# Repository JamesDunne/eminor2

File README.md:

Read more about this project at http://eminor2.bittwiddlers.org/

The repository is split into two versions of the project, v1 and v2.

v1 is the original eminor project created in 2007 and exists as a single prototype unit. Read more about that project here: http://bittwiddlers.org/e-minor/. I continued hacking on this project well into the design and production of v2 so that I could still have a functional MIDI controller. Its code and project files are kept around for posterity now.

v2 corresponds to the more recent eminor2 project, started in 2013. I designed v2 based on the shortcomings of v1, notably the lack of enough footswitches and the physical spacing between the footswitches. The v2 has twice as many footswitches as the v1, and has one LED per each footswitch for simple signalling UX purposes. The v2 also sports a 40x4 character LCD screen which is a notable improvement over the 5x 7-segment LED display on the v1.

Each project folder is split into `controller` and `PCB`. `controller` contains all the C and microcontroller assembly source code for the firmware controller logic. `PCB` contains all the schematics, drawings, and design files for the hardware portion.

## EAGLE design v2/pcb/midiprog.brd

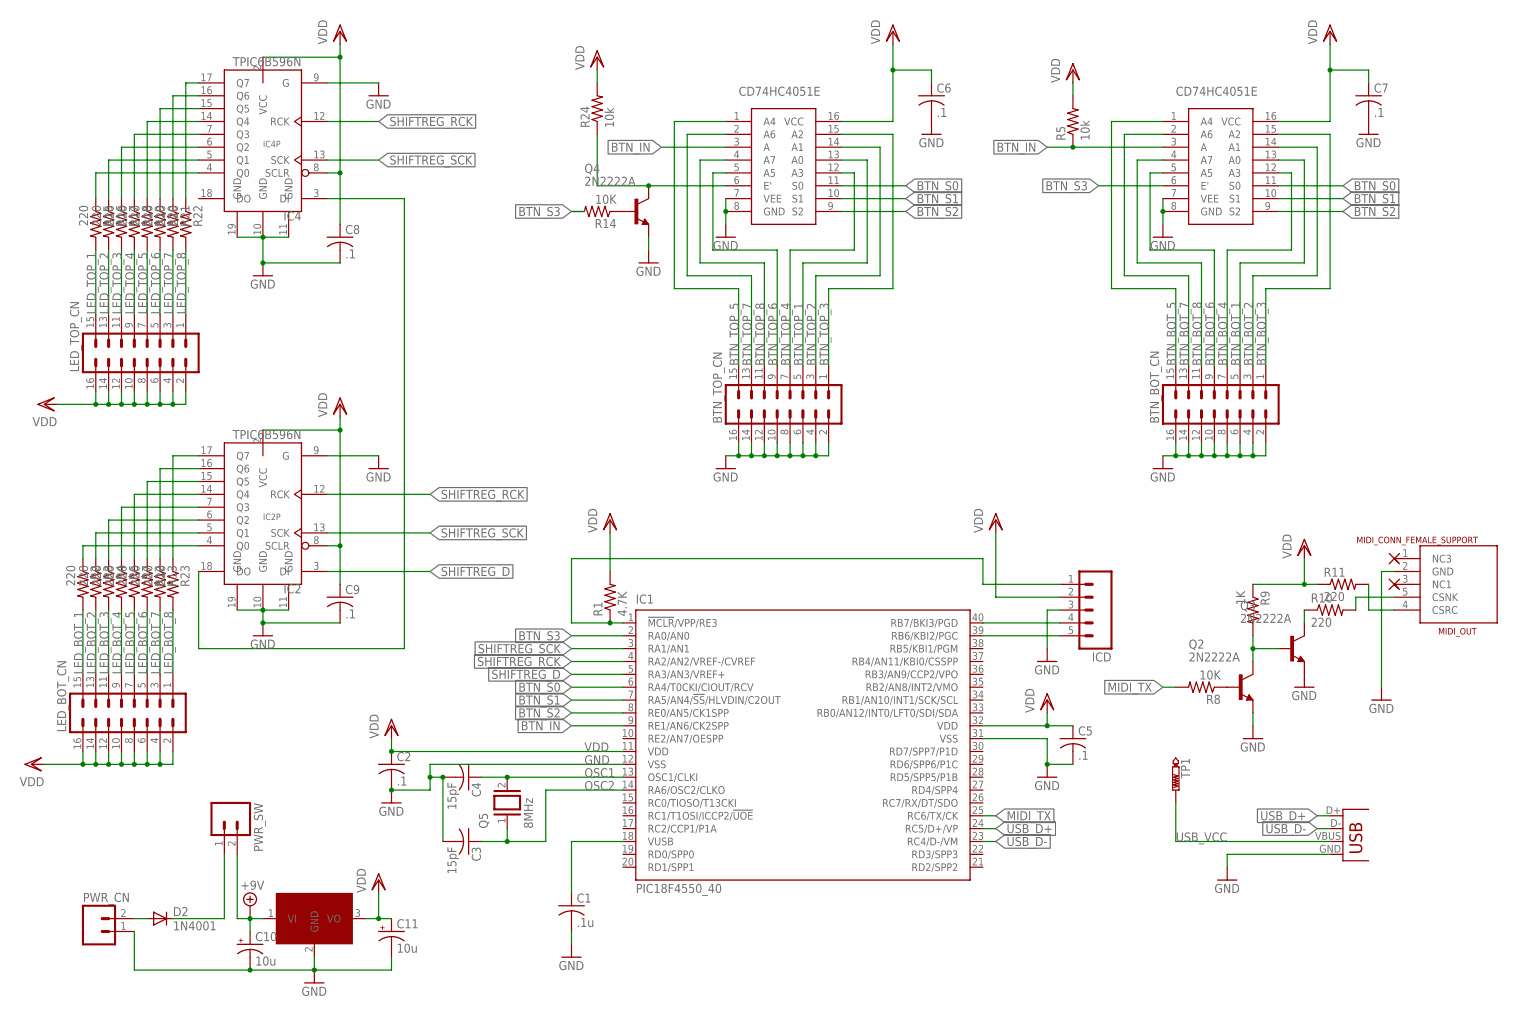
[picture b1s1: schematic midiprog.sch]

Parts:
BTN_BOT_CN: MA08-2
BTN_TOP_CN: MA08-2
C1: .1u; C050-025X075
C2, C5, C6, C7, C8, C9: .1; C050-025X075
C3, C4: 15pF; C050-025X075
C10, C11: 10u; E2,5-6
D2: 1N4001; DO41-10
IC1: PIC18F4550_40; DIL40
IC2, IC4: TPIC6B596N; DIL20
ICD: MA05; 05PA
JP1: USB-B; USB-B-PTH
LED_BOT_CN: MA08-2
LED_TOP_CN: MA08-2
MIDI_OUT: MIDI_CONN_FEMALE_SUPPORT; DIN_5_FEMALE_SUPPORT
PWR_CN: M02; 02P
PWR_SW: M02; 02P
Q2, Q3, Q4: 2N2222A; TO18
Q5: 8MHz; QS
R1: 4.7K; 0207/10
R2, R3, R4, R6, R7, R10, R11, R12, R13, R15, R16, R17, R18, R19, R20, R21, R22, R23: 220; 0207/10
R5, R24: 10k; 0207/10
R8, R14: 10K; 0207/10
R9: 1K; 0207/10
TP1: PTR1PAD1-17; P1-17
U$1, U$2: CD74HC4051E
U$3: 7805; JKDFJD

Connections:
+9V: C10.+, PWR_SW.2, U$3.1 (VI)
BTN_BOT_1: BTN_BOT_CN.5, U$1.13 (A0)
BTN_BOT_2: BTN_BOT_CN.3, U$1.14 (A1)
BTN_BOT_3: BTN_BOT_CN.1, U$1.15 (A2)
BTN_BOT_4: BTN_BOT_CN.7, U$1.12 (A3)
BTN_BOT_5: BTN_BOT_CN.15, U$1.1 (A4)
BTN_BOT_6: BTN_BOT_CN.9, U$1.5 (A5)
BTN_BOT_7: BTN_BOT_CN.13, U$1.2 (A6)
BTN_BOT_8: BTN_BOT_CN.11, U$1.4 (A7)
BTN_IN: IC1.9 (RE1/AN6/CK2SPP), R5.1, U$1.3 (A), U$2.3 (A)
BTN_S0: IC1.6 (RA4/T0CKI/CIOUT/RCV), U$1.11 (S0), U$2.11 (S0)
BTN_S1: IC1.7 (RA5/AN4/!SS!/HLVDIN/C2OUT), U$1.10 (S1), U$2.10 (S1)
BTN_S2: IC1.8 (RE0/AN5/CK1SPP), U$1.9 (S2), U$2.9 (S2)
BTN_S3: IC1.2 (RA0/AN0), R14.2, U$1.6 (E')
BTN_TOP_1: BTN_TOP_CN.5, U$2.13 (A0)
BTN_TOP_2: BTN_TOP_CN.3, U$2.14 (A1)
BTN_TOP_3: BTN_TOP_CN.1, U$2.15 (A2)
BTN_TOP_4: BTN_TOP_CN.7, U$2.12 (A3)
BTN_TOP_5: BTN_TOP_CN.15, U$2.1 (A4)
BTN_TOP_6: BTN_TOP_CN.9, U$2.5 (A5)
BTN_TOP_7: BTN_TOP_CN.13, U$2.2 (A6)
BTN_TOP_8: BTN_TOP_CN.11, U$2.4 (A7)
GND: BTN_BOT_CN.2, BTN_BOT_CN.4, BTN_BOT_CN.6, BTN_BOT_CN.8, BTN_BOT_CN.10, BTN_BOT_CN.12, BTN_BOT_CN.14, BTN_BOT_CN.16, BTN_TOP_CN.2, BTN_TOP_CN.4, BTN_TOP_CN.6, BTN_TOP_CN.8, BTN_TOP_CN.10, BTN_TOP_CN.12, BTN_TOP_CN.14, BTN_TOP_CN.16, C1.2, C2.2, C3.2, C4.2, C5.2, C6.2, C7.2, C8.2, C9.2, C10.-, C11.-, IC1.12 (VSS), IC1.31 (VSS), IC2.9 (G), IC2.10 (GND), IC2.11 (GND), IC2.19 (GND), IC4.9 (G), IC4.10 (GND), IC4.11 (GND), IC4.19 (GND), ICD.3, JP1.GND, MIDI_OUT.2 (GND), PWR_CN.1, Q2.1 (E), Q3.1 (E), Q4.1 (E), U$1.7 (VEE), U$1.8 (GND), U$2.7 (VEE), U$2.8 (GND), U$3.2 (GND)
LED_BOT_1: LED_BOT_CN.15, R2.2
LED_BOT_2: LED_BOT_CN.13, R3.2
LED_BOT_3: LED_BOT_CN.11, R4.2
LED_BOT_4: LED_BOT_CN.9, R6.2
LED_BOT_5: LED_BOT_CN.7, R7.2
LED_BOT_6: LED_BOT_CN.5, R12.2
LED_BOT_7: LED_BOT_CN.3, R13.2
LED_BOT_8: LED_BOT_CN.1, R23.2
LED_TOP_1: LED_TOP_CN.15, R15.2
LED_TOP_2: LED_TOP_CN.13, R16.2
LED_TOP_3: LED_TOP_CN.11, R17.2
LED_TOP_4: LED_TOP_CN.9, R18.2
LED_TOP_5: LED_TOP_CN.7, R19.2
LED_TOP_6: LED_TOP_CN.5, R20.2
LED_TOP_7: LED_TOP_CN.3, R21.2
LED_TOP_8: LED_TOP_CN.1, R22.2
MIDI_TX: IC1.25 (RC6/TX/CK), R8.2
unnamed: IC1.1 (!MCLR!/VPP/RE3), ICD.1, R1.1
unnamed: Q2.2 (B), R8.1
unnamed: Q2.3 (C), Q3.2 (B), R9.2
unnamed: Q3.3 (C), R10.1
unnamed: MIDI_OUT.4 (CSRC), R11.2
unnamed: MIDI_OUT.5 (CSNK), R10.2
unnamed: IC1.39 (RB6/KBI2/PGC), ICD.5
unnamed: IC1.40 (RB7/BKI3/PGD), ICD.4
unnamed: C1.1, IC1.18 (VUSB)
unnamed: IC4.4 (Q0), R15.1
unnamed: IC4.5 (Q1), R16.1
unnamed: IC4.6 (Q2), R17.1
unnamed: IC4.7 (Q3), R18.1
unnamed: IC4.14 (Q4), R19.1
unnamed: IC4.15 (Q5), R20.1
unnamed: IC4.16 (Q6), R21.1
unnamed: IC4.17 (Q7), R22.1
unnamed: IC2.18 (DO), IC4.3 (DI)
unnamed: D2.A, PWR_CN.2
unnamed: D2.C, PWR_SW.1
unnamed: IC2.4 (Q0), R2.1
unnamed: IC2.5 (Q1), R3.1
unnamed: IC2.6 (Q2), R4.1
unnamed: IC2.7 (Q3), R6.1
unnamed: IC2.14 (Q4), R7.1
unnamed: IC2.15 (Q5), R12.1
unnamed: IC2.16 (Q6), R13.1
unnamed: IC2.17 (Q7), R23.1
unnamed: Q4.2 (B), R14.1
unnamed: Q4.3 (C), R24.1, U$2.6 (E')
OSC1: C4.1, IC1.13 (OSC1/CLKI), Q5.2
OSC2: C3.1, IC1.14 (RA6/OSC2/CLKO), Q5.1
SHIFTREG_D: IC1.5 (RA3/AN3/VREF+), IC2.3 (DI)
SHIFTREG_RCK: IC1.4 (RA2/AN2/VREF-/CVREF), IC2.12 (RCK), IC4.12 (RCK)
SHIFTREG_SCK: IC1.3 (RA1/AN1), IC2.13 (SCK), IC4.13 (SCK)
USB_D+: IC1.24 (RC5/D+/VP), JP1.D+
USB_D-: IC1.23 (RC4/D-/VM), JP1.D-
USB_VCC: JP1.VBUS, TP1.TP
VDD: C2.1, C5.1, C6.1, C7.1, C8.1, C9.1, C11.+, IC1.11 (VDD), IC1.32 (VDD), IC2.2 (VCC), IC2.8 (SCLR), IC4.2 (VCC), IC4.8 (SCLR), ICD.2, LED_BOT_CN.2, LED_BOT_CN.4, LED_BOT_CN.6, LED_BOT_CN.8, LED_BOT_CN.10, LED_BOT_CN.12, LED_BOT_CN.14, LED_BOT_CN.16, LED_TOP_CN.2, LED_TOP_CN.4, LED_TOP_CN.6, LED_TOP_CN.8, LED_TOP_CN.10, LED_TOP_CN.12, LED_TOP_CN.14, LED_TOP_CN.16, R1.2, R5.2, R9.1, R11.1, R24.2, U$1.16 (VCC), U$2.16 (VCC), U$3.3 (VO)

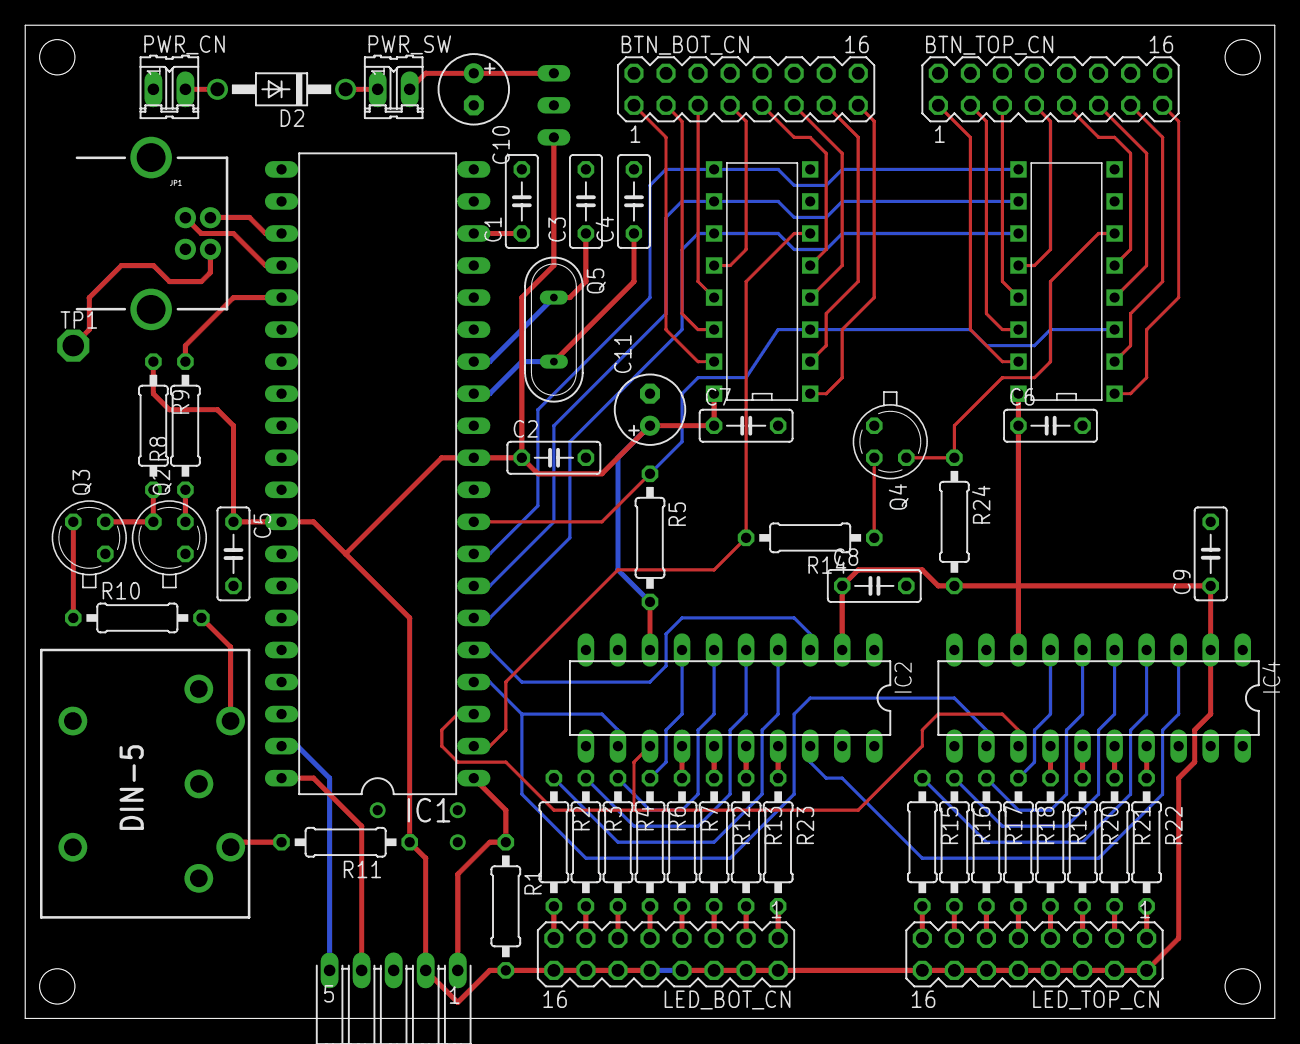
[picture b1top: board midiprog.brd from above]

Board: 2 copper layers, 99.1 x 78.7 mm, 56 parts (0 on the bottom side), 79 nets.

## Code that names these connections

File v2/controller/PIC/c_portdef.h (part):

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
//PORTA Definitions
#define BTN_S3_BIT                      0
#define BTN_S3_PIN                      PORTAbits.RA0   //Pin 2
#define BTN_S3_LAT_BIT                  LATAbits.LATA0
#define BTN_S3_LAT                      LATA
#define BTN_S3_TRIS_BIT                 TRISAbits.TRISA0
#define BTN_S3_PORT                     PORTA
#define TRISAPIN0                       (OUTPUT<<0)
#define LATAPIN0                        (false<<0)

#define SHIFTREG_SRCK_BIT               1
#define SHIFTREG_SRCK_PIN               PORTAbits.RA1   //Pin 3
#define SHIFTREG_SRCK_LAT_BIT           LATAbits.LATA1
#define SHIFTREG_SRCK_LAT               LATA
#define SHIFTREG_SRCK_TRIS_BIT          TRISAbits.TRISA1
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#define LATAPIN1                        (false<<1)

#define SHIFTREG_RCK_BIT                2
#define SHIFTREG_RCK_PIN                PORTAbits.RA2   //Pin 4
#define SHIFTREG_RCK_LAT_BIT            LATAbits.LATA2
#define SHIFTREG_RCK_LAT                LATA
#define SHIFTREG_RCK_TRIS_BIT           TRISAbits.TRISA2
#define SHIFTREG_RCK_PORT               PORTA
#define TRISAPIN2                       (OUTPUT<<2)
#define LATAPIN2                        (false<<2)

#define SHIFTREG_SER_IN_BIT             3
#define SHIFTREG_SER_IN_PIN             PORTAbits.RA3   //Pin 5
#define SHIFTREG_SER_IN_LAT_BIT         LATAbits.LATA3
#define SHIFTREG_SER_IN_LAT             LATA
#define SHIFTREG_SER_IN_TRIS_BIT        TRISAbits.TRISA3
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#define LATAPIN3                        (false<<3)

#define BTN_S0_BIT                      4
#define BTN_S0_PIN                      PORTAbits.RA4   //Pin 6
#define BTN_S0_LAT_BIT                  LATAbits.LATA4
#define BTN_S0_LAT                      LATA
#define BTN_S0_TRIS_BIT                 TRISAbits.TRISA4
#define BTN_S0_PORT                     PORTA
#define TRISAPIN4                       (OUTPUT<<4)
#define LATAPIN4                        (false<<4)

#define BTN_S1_BIT                      5
#define BTN_S1_PIN                      PORTAbits.RA5   //Pin 7
#define BTN_S1_LAT_BIT                  LATAbits.LATA5
#define BTN_S1_LAT                      LATA
#define BTN_S1_TRIS_BIT                 TRISAbits.TRISA5
#define BTN_S1_PORT                     PORTA
#define TRISAPIN5                       (OUTPUT<<5)
#define LATAPIN5                        (false<<5)

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#define LATBPIN5                        (false<<5)

#define UNUSED1_OFF_BIT                 6
#define UNUSED1_PIN                     PORTBbits.RB6   //Pin 39
#define UNUSED1_LAT_BIT                 LATBbits.LATB6
#define UNUSED1_LAT                     LATB
#define UNUSED1_TRIS_BIT                TRISBbits.TRISB6
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#define LATBPIN6                        (false<<6)

#define UNUSED2_BIT                     7
#define UNUSED2_PIN                     PORTBbits.RB7   //Pin 40
#define UNUSED2_LAT_BIT                 LATBbits.LATB7
#define UNUSED2_LAT                     LATB
#define UNUSED2_TRIS_BIT                TRISBbits.TRISB7
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#define LATCPIN3                        (false<<3)

#define USBDM_BIT                       4
#define USBDM_PIN                       PORTCbits.RC4   //Pin 23
#define USBDM_LAT_BIT                   LATCbits.LATC4
#define USBDM_LAT                       LATC
#define USBDM_TRIS_BIT                  TRISCbits.TRISC4
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#define LATCPIN4                        (false<<4)

#define USBDP_BIT                       5
#define USBDP_PIN                       PORTCbits.RC5   //Pin 24
#define USBDP_LAT_BIT                   LATCbits.LATC5
#define USBDP_LAT                       LATC
#define USBDP_TRIS_BIT                  TRISCbits.TRISC5
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#define LATCPIN5                        (false<<5)

#define TX_BIT                          6
#define TX_PIN                          PORTCbits.RC6   //Pin 25
#define TX_LAT_BIT                      LATCbits.LATC6
#define TX_LAT                          LATC
#define TX_TRIS_BIT                     TRISCbits.TRISC6
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//++++++++++++++++++++++++++++++++++++++++++++++++++++++++++++++++++++++++++++++
//PORTE Definitions
#define BTN_S2_BIT                      0
#define BTN_S2_PIN                      PORTEbits.RE0   //Pin 8
#define BTN_S2_LAT_BIT                  LATEbits.LATE0
#define BTN_S2_LAT                      LATE
#define BTN_S2_TRIS_BIT                 TRISEbits.TRISE0
#define BTN_S2_PORT                     PORTE
#define TRISEPIN0                       (OUTPUT<<0)
#define LATEPIN0                        (false<<0)

#define BTN_IN_BIT                      1
#define BTN_IN_PIN                      PORTEbits.RE1   //Pin 9
#define BTN_IN_LAT_BIT                  LATEbits.LATE1
#define BTN_IN_LAT                      LATE
#define BTN_IN_TRIS_BIT                 TRISEbits.TRISE1
#define BTN_IN_PORT                     PORTE
#define TRISEPIN1                       (INPUT<<1)
#define LATEPIN1                        (false<<1)

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
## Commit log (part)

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2017-07-05 Allow unnamed songs to be editable.
2017-07-05 Recompiled html5.
2017-07-05 Rebuilt HEX.
2017-08-01 Updated setlist for next show. Rebuilt HEX.
2017-08-01 Updated venue
2017-08-05 Rebuilt on new install as test. Updated project with relative paths instead of hard-coded C:\ paths.
2017-08-13 Updated axe-fx
2017-08-13 Updated axe-fx to match black album tone
2017-08-13 Updated tone slightly
2017-08-13 Fix win32 midi device number in debug settings
2017-08-15 Ideal Sandman tone
2017-08-15 Improved input trim curve to not cause clean sound to clip too much
2017-08-16 Switched Win32 driver to parse MIDI out device by name from command line.
2017-08-16 Save before tweak
2017-08-16 Closer to sandman... need more low end, less mid.
2017-08-16 Fixed Trippin
2017-08-16 Log-taper the gain from the yaml file; TODO make this permanent.
2017-08-16 Fix volume curves, gates, and compressor settings.
2017-08-16 Rebuilt HEX
2017-08-17 Even closer
2017-08-17 Less harshness in upper mids.
2017-08-17 Perfect
2017-08-21 Fixed html5 bug in formatting signed 8-bit values as hex.
2017-08-21 Require allow/block MIDI access before starting controller.
2017-08-21 Fix midi log width
2017-08-21 Working midi send.
2017-08-22 Upgraded volume curves on amps.
2017-08-22 Drop-down to select MIDI device.
2017-09-06 flash_manager now generates songs.tsv
2017-09-06 Updated headers.
2017-09-07 New setlist
2017-09-22 Fix toolset
2017-09-22 Remove old flash_manager.
2017-09-22 Set up Win32 project.
2017-09-22 Set up PIC build
2017-09-22 Reorganize functions.
2017-09-22 Tweaked LCD design; added design of custom FX selector.
2017-09-22 Redesigned AMP controls slightly for quicker access to more commonly used features (reset volume or gain to default)
2017-09-22 Document Axe-FX changes a bit better; TODOs for desired features.
2017-09-22 Clarified gain store/recall behavior. Consistency on other screens.
2017-09-22 Clarify FX selection behavior and LCD response.
2017-09-23 Update axe-fx programs and create new v5.
2017-09-23 Update v5 axe-fx
2017-09-23 Dont assume PITCH effect due to high CPU usage of basic 2-amp template.
2017-09-23 Starting to make row modes.
2017-09-25 Rewrote portion of button control; FX enable/disable and clean/dirty/acoustic switch
2017-09-25 Remove XY code
2017-09-25 chmod +x
2017-09-25 Fix compiler errors
2017-09-25 Implemented main AMP controls.
2017-09-25 Update html5 build for v5
2017-09-25 Fixed bugs.
2017-09-25 Fix dumb bugs on LCD.
2017-09-25 Correct release semantics depending on oneshot or repeater. Disable acoustic when tap on clean/dirty.
2017-09-25 Highlight LED of button indicating < or > gain or volume.
2017-09-26 Recompiled html5
2017-09-26 Fixed XY behavior for clean/dirty vs. acoustic. Fixed bad CC number.
2017-09-26 Fix LCD display
2017-09-26 Fix LCD display with fx
2017-09-26 Keep FX LED on in FX mode.
2017-09-26 make debug reload to reload current chrome tab
2017-09-30 Moved program-specific structs out to separate .h file to be reused by flash_manager.
2017-09-30 Updates for vs_code
2017-09-30 Fixed separation concerns.
2017-09-30 Added custom fx_layouts
2017-09-30 Move BankedWriter out to separate file.
2017-09-30 Fix FX names to be for amp1 or 2.
2017-09-30 Rebuilt PIC flash banks.
2017-09-30 Fix NUL char to write as 0.
2017-10-01 Recompile html5
2017-10-01 Redefine set_list structure to allow 127 songs and remove date since it is not displayed any longer.
2017-10-01 Corrected flash addresses to load/store; relaxed flash_load constraints regarding 64-byte boundary.
2017-10-01 Fix bug counting setlist size.
2017-10-01 Split gain to gain_log; evaluate default logic.
2017-10-01 Fix off by one bug in song count display; update LCD when toggle mode.
2017-10-01 Add scene_count field.
2017-10-01 Show scene count on LCD
2017-10-01 Fix macro bug
2017-10-02 Fix hardware flash size for html5.
2017-10-03 Send FX MIDI changes; document amp changing MIDI.
2017-10-21 Removed selected_amp state.
2017-10-21 Set/restore default gain is a bad idea.
2017-10-21 Fix toggle acoustic off to not flip clean/dirty as well.
2017-10-21 Moved rowstate into state
2017-10-21 Start of changing button labels when switching to FX mode.
2017-10-21 Shortened fx names to 4 chars for display on LCD and HWLABELS.
2017-10-21 Fix debug log of fx name.
2017-10-21 Fixups for PIC build.
2017-10-24 Remove SAVE function, replace with TAP|MODE. Remove incomplete SELECTFX mode. Upper/lowercase FX names based on enabled/disabled.
2017-10-24 Update PIC
2017-10-24 Cleaning up #pragmas for PIC and cutting down ROM+RAM requirements.
2017-10-24 Fix PIC ROM pages so that flash is set at correct offset for 12KB length.
2017-10-24 Condensed code by not requiring mode_leds array.
2017-10-24 Upper/lowercase letters on AMP row for FX.
2017-10-25 Fixed flash manager to use same names.
2017-10-25 Rebuilt PIC
2017-10-25 Tiny code size improvements.
2017-10-25 More tiny improvements.
2017-10-25 Tightening up code memory.
2017-11-09 Removed redundant Kids entry.
2017-11-09 Create new set list
2017-11-17 Fixed gate bug when switching between acoustic and electric.
2017-11-17 Recompile html
2017-11-18 Reduce acoustic gain to avoid clipping.
2017-11-18 Keeping Axe-FX patches.
2017-11-18 Fix clean/acoustic switching so clean uses amp Y.
2017-11-18 Add new Axe-FX presets.
2017-11-25 Disable amp for acoustic. Start using global variable for clean_gain adjustment.
2017-11-25 Use original midi program numbers now.
2017-11-25 Updated Axe-FX MIDI OUT name; it changed for some reason.
2017-12-01 Added Sandman tone.
2017-12-01 Added new set list.
2017-12-01 Update setlist order.
2017-12-01 Update setlists
2017-12-02 Updated setlist to remove acoustic set.
2018-02-05 Remove binary
2018-02-05 Added new songs Creep and Go My Way
2018-02-28 Rebuilt HEX for v1
2018-03-01 ASCII art
2018-03-08 Rebuild html5
2018-03-14 Starting work on flexible amp channels regarding what CCs to enable/disable for amp channel switching.
2018-03-14 Build html5
2018-03-28 Added new set list
2018-03-28 Remove a few unused songs.
2018-04-12 Dump of new v8 tones - highlight is puppets using new Silent Underground Puppets FW Q9.04.
2018-05-18 Updated puppets v8
2018-08-08 Updated programs, new setlist.
2018-08-08 Updated HEX build
2018-08-13 Replace TAP with previous scene.
2018-08-13 Fix bad code
2018-08-15 Update clean gain from 0x10 to 0x12.
2018-08-22 Only allow next/prev scene after a retrigger timeout.
2018-09-26 Minor program tweaks for better balance.
2018-09-26 New setlist.
2018-12-12 Added new setlist; added new programs for Under the Bridge and Slide.
2018-12-12 Updated HEX
2019-02-06 Added new setlist for 2/23
2019-02-17 Replaced phasers with flangers for better Crawling tone.
2019-02-17 Updated html5 Makefile to include PIC headers.
2019-02-23 Moved Lump in setlist
2019-02-23 Build HEX
2019-04-24 Updated html5 build
2019-04-30 Rebuild html5.
2019-05-03 Updated Fuel gain and volumes
2019-05-04 Updated Puppets settings
2019-05-15 New set list
2019-05-15 Update html5 build
2019-05-15 Updated label for SCENE-- button
2019-06-04 Created setlist-generator and updated song-names.yml to mark deprecated songs.
2019-06-04 Clip shuffled song list to commandline argument as integer
2019-06-16 Updated song list for private party
2019-06-20 Added new setlist
2019-06-29 Add default gate setting at song level.
2019-06-29 Reduce default gate to -42dB
2019-07-01 Compilable v6
2019-07-01 Restructured amp_defaults to be shared between both amps.
2019-07-01 Write new flash_manager_v6 to emit v6 compatible headers.
2019-07-01 Fix padding issues
2019-07-01 Assert offsets of romdata fields
2019-07-01 Generate PIC headers
2019-07-01 Update html5 build to actually use v6 headers
2019-07-01 Fix bug with not setting sent CC values in cache.
2019-07-01 Zero out gate valuess
2019-07-01 Convert gate threshold from dB to MIDI
2019-07-01 Fix html5 sysex bug where messages were not clearing between F7 to F0
2019-07-01 Reintroduce BYP of GATE block instead of setting threshold down to a minimal value
2019-07-01 Make song-default gain and gate actually apply
2019-07-01 Fix PIC build but has buggy LCD display
2019-07-02 Small update
2019-07-02 Fix inc/dec from 0 bug
2019-07-02 Saving code space by converting macros to functions
2019-07-02 Translate gain_log to gain in v6
2019-07-02 Rebuild PIC
2019-07-02 Add td50_midi mappings to change drum kits per song
2019-07-02 Rebuilt HEX with slight code savings
2019-07-02 Designing and documenting new interface layout
2019-07-03 Remove unused bits
2019-07-03 Revert "Simplify calc_midi"
    This reverts commit c143f57dda9c36dfec1121d6a864a09828f087e9.
2019-07-03 Simple code reuse for LCD AMP rows
2019-07-03 Switch LCD amp rows to new design
2019-07-03 Implemented button and LED logic for new control layouts
2019-07-03 Fix AMP|FX toggle in MIDI screen
2019-07-03 Fix MIDI inc/dec logic to respect bounds
2019-07-03 Swapped GATE and VOLU button pairs. Removing extra timers not needed.
2019-07-03 Tiny effort to conserve code space on PIC
2019-07-03 Update HEX
2019-07-03 Fix html5 build to include left/right arrow chars from LCD charset.
2019-07-06 Updated Win32 build
2019-07-06 Enable extended-mode for PIC18 build.
2019-07-06 Revert "Enable extended-mode for PIC18 build."
    This reverts commit 284a6e4c9860e963f2dde31ccaf276411839a0cd.
2019-07-06 Remove calculation of modified status; added load_axe_midi() function and calls to it to reload axe_midi pointer when modifying axe_midi_program.
2019-07-06 Updated PIC build
2019-07-06 Consistent near pointers; did not have any effect on code size though
2019-07-06 Use anonymous struct within union to make u16 copies of io16 easier.
2019-07-06 Rebuilt HEX; saved code space with u16 in union
2019-07-06 Resize midi log display in html5
2019-07-06 Add TODO items
2019-07-06 Update controller logic to expect only 4 FX instead of 5.
2019-07-06 Add buttons in FX screen to toggle using default gain, gate, and volume.
2019-07-06 Removed unused functions
2019-07-06 Update TODO items and screens
2019-07-06 Allow selecting new song without activating scene 1 until scene++ button is pressed.
2019-07-06 Remove song_name pointer in favor next_pr_num
2019-07-06 Fix song_name declaration
2019-07-08 Upgrade html5 to use B key from USB footswitch to bind to SCENE++ button.
2019-07-09 Extended mode is bad and failed to start, might be due to bootloader embedded code.
2019-07-09 Implemented midi_send_sysex_buffer for PIC
2019-07-10 Remove old flash managers
2019-07-10 Fixed bug with setting lowest gate value at 0 instead of 1
2019-07-10 Limit song number to max_song_count
2019-07-10 Initialize defaults for uninitialized songs
2019-07-12 Corrected alternative ritoa implementation with simple unit test program.
2019-07-14 Implement simple time marker delta and interval tracking system to make TAP TEMPO LED blink in tempo.
2019-07-15 Add timer support to PIC hwcalls.c and systick.c; UNTESTED
2019-07-29 Corrected timer to use 1ms ticks instead of 10ms ticks.
2019-07-30 Add LOOPER screen with buttons and LEDs.
2019-07-30 Made PIC backend sensitive to WRITABLE_SEG_LEN in all but linker file. Updated flash_manager_v6 to also use flash.h definitions.
2019-07-30 Added LCD data sheet
2019-07-30 Tighten up timing for handling buttons, LEDs, and controller code
2019-07-30 Debounce buttons properly to 125msec and responding to button-down events within 1msec.
2019-07-31 Update html5
2019-07-31 New setlist and updated programs for gate and leveling
2019-07-31 Update repeater timers; need to add debounce release feature.
2019-08-02 Rename bypass to enable for looper since that makes more sense the way its used.
2019-08-02 Set looper ONCE button to be edge triggered and time LED/LCD update to 400ms delay
2019-08-02 Rebuilt HEX; reduced flash size to accomodate code
2019-08-02 Remove looper_state from curr/last pair
2019-08-03 Corrected debounce/rebounce logic
2019-08-03 Updated gate settings for MG
2019-08-03 Update setlist-generator to use v6 and limit max of cmdline arg
2019-08-16 Added artist names to song-names.yml
2019-08-16 Added YouTube links to song-names.yml
2019-08-27 Added Mysterious Ways song

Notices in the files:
parts and their libraries:
SparkFun-Connectors-fdb4deb3ddf02d02ceca: Licensing: CC v3.0 Share-Alike You are welcome to use this library for commercial purposes.
